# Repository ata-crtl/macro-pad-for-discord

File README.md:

# Discord Macro Keyboard

A customdesigned discordmacro keyboard with complete PCB design. Features include ,discord shortcut keys for quick messaging and commands during gameplay or streaming.

## Why I Made This Project

I created this discord macro keyboard to streamline my discord experience during gaming sessions and streaming. Having dedicated physical buttons for common discord commands removes the need to alt-tab or memorize  keyboard shortcuts  allowing me to stay focu#

## Bill of Materials (BOM)

| Part | Quantity | Description | Source |
|------|----------|-------------|--------|
| **Seeed XIAO RP2040** | 1 | Approved microcontroller, QMK compatible, RP2040 @ 133MHz | [The Pi Hut](https://thepihut.com/products/seeed-xiao-rp2040) |
| **OLED Display (0.96" I2C)** | 1 | 128x64 resolution OLED for status display | [Seeed Studio](https://www.seeedstudio.com) or [The Pi Hut](https://thepihut.com) |
| **Rotary Encoder (20mm)** | 1 | 24-step encoder with push button, 6mm shaft | [Switch Electronics](https://www.switchelectronics.co.uk/products/20mm-rotary-encoder-with-switch-6mm-splined-shaft) |
| **Mechanical Switches (Cherry MX)** | 4 | 4x Cherry MX compatible switches (linear/tactile) | [SerpentKeys UK](https://www.serpentkeys.co.uk/collections/switches) |
| **Cherry Keycaps** | 4 | 4x Cherry-compatible keycaps (various colors) | [CustomKeyCaps UK](https://www.customkeycaps.co.uk) or [Overclockers UK](https://www.overclockers.co.uk/peripherals/keyboards/custom-keyboards/keycaps/pbt-keycaps) |
| **3mm LED (Red)** | 1 | Status indicator LED | [Switch Electronics](https://www.switchelectronics.co.uk/products/3mm-leds) or [CPC UK](https://cpc.farnell.com) |
| **3mm LED (Blue)** | 1 | Secondary status indicator LED | [Switch Electronics](https://www.switchelectronics.co.uk/products/3mm-leds) or [CPC UK](https://cpc.farnell.com) |
| **1N4148 Diodes** | 4 | Signal diodes for keyboard matrix | [Switch Electronics](https://www.switchelectronics.co.uk/products/1n4148-small-signal-diode-100v-150ma-pack-of-10) |
| **10kΩ Resistors (0805)** | 6 | Pull-up resistors for encoder and buttons | [Amazon UK](https://www.amazon.co.uk) |
| **220Ω Resistors (0805)** | 2 | Current limiting for LEDs | [Amazon UK](https://www.amazon.co.uk) |
| **0.1µF Capacitors (0805)** | 2 | Decoupling capacitors for stable power | [Amazon UK](https://www.amazon.co.uk) |
| **PCB** | 1 | Custom 2-layer PCB with castellated pads | [JLCPCB](https://jlcpcb.com/) |
| **M2x6mm Screws & Nuts** | 4 sets | Mounting hardware for case | [Amazon UK](https://www.amazon.co.uk) |
| **USB-C Cable (1m)** | 1 | USB-C to USB-A cable, Anker brand | [Amazon UK](https://www.amazon.co.uk) |
| **3D Printed Case** | 1 | Custom enclosure (PLA, self-printed or service) | [3DPrintUK](https://www.3dprint-uk.co.uk) or [MakeitQuick](https://makeitquick.co.uk) |
| **3M VHB Tape** | 1 roll | Double-sided mounting tape for PCB | [Amazon UK](https://www.amazon.co.uk) |

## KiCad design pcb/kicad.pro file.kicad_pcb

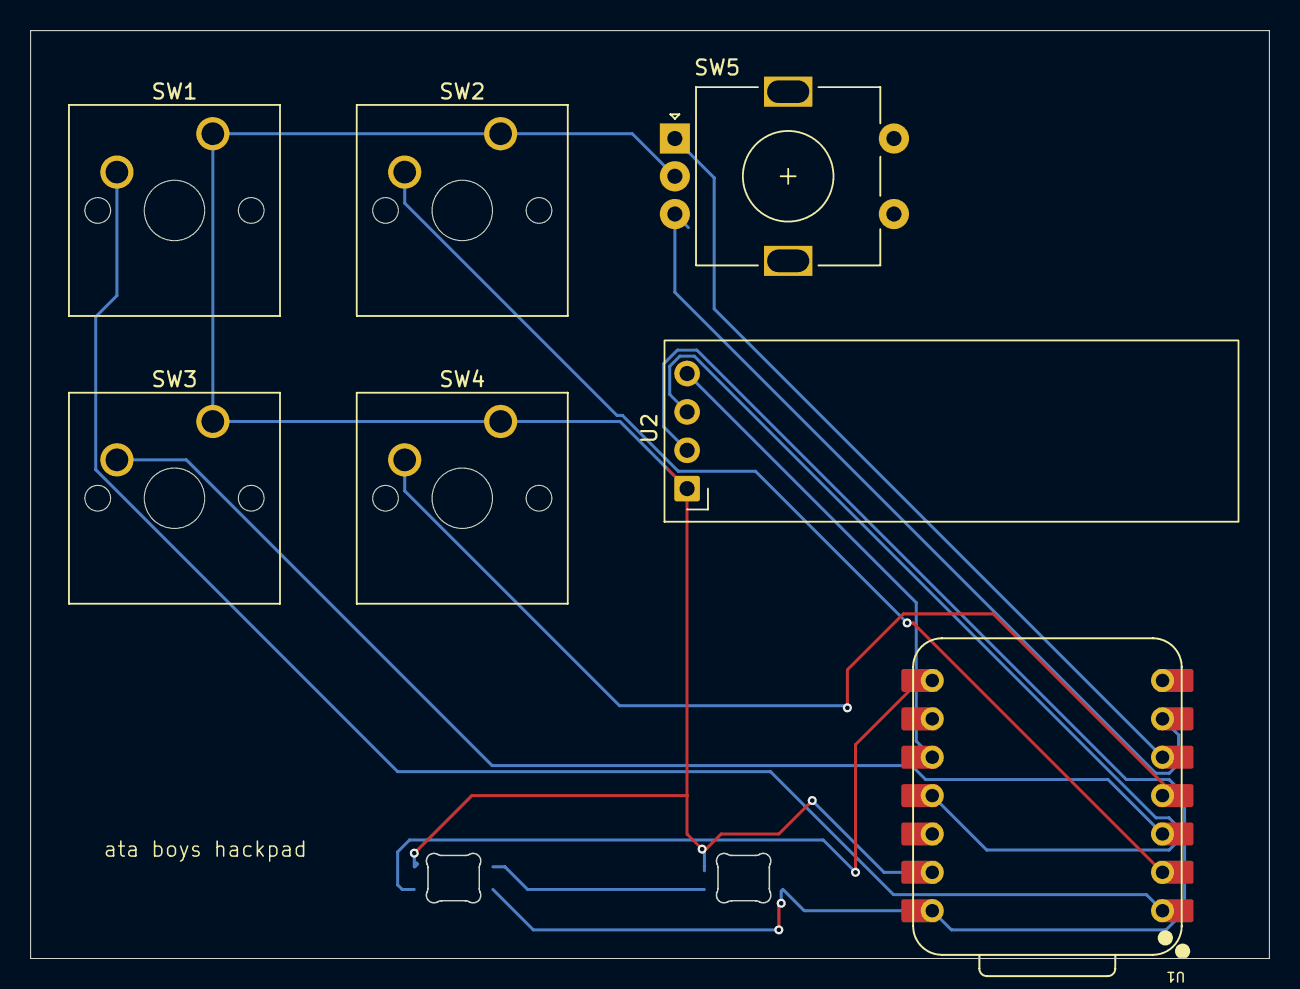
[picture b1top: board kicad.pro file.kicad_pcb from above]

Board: 2 copper layers, 82.0 x 61.4 mm, 9 parts (0 on the bottom side), 12 nets.

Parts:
D1, D2: SK6812MINI-E; MX_SK6812MINI-E_REV
SW1, SW2, SW3, SW4: SW_Push; SW_Cherry_MX_1.00u_PCB
SW5: RotaryEncoder; RotaryEncoder_Alps_EC11E-Switch_Vertical_H20mm
U1: XIAO-RP2040-DIP
U2: OLED_0.91_128x32

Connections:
+5V: D1.1 (VDD), D2.1 (VDD), U1.14 (VBUS), U2.2 (VCC)
GND: D1.3 (VSS), D2.3 (VSS), SW1.1, SW2.1, SW3.1, SW4.1, SW5.C, U1.13 (GND), U2.1 (GND)
unnamed: D1.4 (DIN), U1.8 (GPIO1/RX)
unnamed: D1.2 (DOUT), D2.4 (DIN)
unnamed: U1.11 (GPIO3/MOSI), U2.3 (SCL)
unnamed: U1.10 (GPIO4/MISO), U2.4 (SDA)
unnamed: SW5.A, U1.5 (GPIO6/SDA)
unnamed: SW5.B, U1.6 (GPIO7/SCL)
unnamed: SW1.2, U1.1 (GPIO26/ADC0/A0)
unnamed: SW2.2, U1.2 (GPIO27/ADC1/A1)
unnamed: SW3.2, U1.3 (GPIO28/ADC2/A2)
unnamed: SW4.2, U1.4 (GPIO29/ADC3/A3)

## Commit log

2026-02-07 Create production
2026-02-07 Create gerber
2026-02-07 Create cases
2026-02-07 Create py
2026-02-07 Create pc
2026-02-07 Create bod
2026-02-14 Create hg
2026-02-16 Update and rename Configuration 2.step to cad file
